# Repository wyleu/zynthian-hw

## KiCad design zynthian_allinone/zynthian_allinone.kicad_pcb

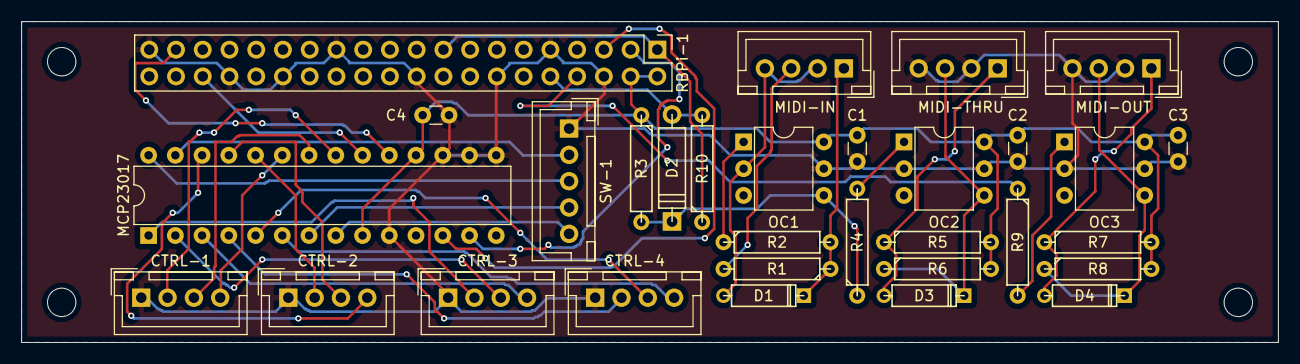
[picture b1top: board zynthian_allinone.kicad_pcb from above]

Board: 2 copper layers, 119.4 x 30.5 mm, 35 parts (0 on the bottom side), 36 nets.

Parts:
C1, C2, C3, C4: 100n; C_Disc_D3.0mm_W1.6mm_P2.50mm
CTRL-1: CTRL1; JST_XH_B04B-XH-A_04x2.50mm_Straight
CTRL-2: CTRL2; JST_XH_B04B-XH-A_04x2.50mm_Straight
CTRL-3: CTRL3; JST_XH_B04B-XH-A_04x2.50mm_Straight
CTRL-4: CTRL4; JST_XH_B04B-XH-A_04x2.50mm_Straight
D1, D3, D4: 1N4148; D3
D2: 1N5819; D4
MCP23017: MCP23017; DIP-28_W7.62mm
MH1, MH2, MH3, MH4: MountingHole_2.7mm_M2.5_DIN965
MIDI-1: MIDI-IN; JST_XH_B04B-XH-A_04x2.50mm_Straight
MIDI-2: MIDI-THRU; JST_XH_B04B-XH-A_04x2.50mm_Straight
MIDI-3: MIDI-OUT; JST_XH_B04B-XH-A_04x2.50mm_Straight
OC1, OC2, OC3: H11L1; DIP-6_W7.62mm
R1: 100; R4
R2, R6, R8: 470; R4
R3, R4, R9: 1K; R4
R5, R7: 4K7; R4
R10: 10K; R4
RBPi-1: RBPi GPIO; Pin_Header_Straight_2x20_Pitch2.54mm
SW-1: SW1; JST_XH_B05B-XH-A_05x2.50mm_Straight

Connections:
+3V3: R10.1, RBPi-1.1, RBPi-1.17
+5V: C1.1, C2.1, C3.1, C4.1, MCP23017.9, MCP23017.18, OC1.6, OC2.6, OC3.6, R3.1, R5.2, R6.2, R7.2, R8.2, RBPi-1.2, RBPi-1.4
/INTA: MCP23017.20, RBPi-1.36
/INTB: MCP23017.19, RBPi-1.37
/MIDI-IN: D2.2, R10.2, RBPi-1.10
/MIDI-OUT: R9.1, RBPi-1.8
/MIDI-THRU: OC2.1, R4.2
GND: C1.2, C2.2, C3.2, C4.2, CTRL-1.1, CTRL-2.1, CTRL-3.1, CTRL-4.1, MCP23017.10, MCP23017.15, MCP23017.16, MCP23017.17, MIDI-2.2, MIDI-2.4, MIDI-3.2, MIDI-3.4, OC1.5, OC2.2, OC2.5, OC3.2, OC3.5, RBPi-1.6, RBPi-1.9, RBPi-1.14, RBPi-1.20, RBPi-1.25, RBPi-1.30, RBPi-1.34, RBPi-1.39, SW-1.1
unnamed: CTRL-1.2, MCP23017.21
unnamed: CTRL-1.3, MCP23017.22
unnamed: CTRL-1.4, MCP23017.23
unnamed: CTRL-2.2, MCP23017.24
unnamed: CTRL-2.3, MCP23017.25
unnamed: CTRL-2.4, MCP23017.26
unnamed: CTRL-3.2, MCP23017.1
unnamed: CTRL-3.3, MCP23017.2
unnamed: CTRL-3.4, MCP23017.3
unnamed: CTRL-4.2, MCP23017.4
unnamed: CTRL-4.3, MCP23017.5
unnamed: CTRL-4.4, MCP23017.6
unnamed: D1.1, MIDI-1.1, R1.1, R2.2
unnamed: D1.2, MIDI-1.2, MIDI-1.4, OC1.2
unnamed: D2.1, OC1.4, R3.2, R4.1
unnamed: D3.1, MIDI-2.3, OC2.4, R6.1
unnamed: D3.2, MIDI-2.1, R5.1
unnamed: D4.1, MIDI-3.3, OC3.4, R8.1
unnamed: D4.2, MIDI-3.1, R7.1
unnamed: MCP23017.7, SW-1.4
unnamed: MCP23017.8, SW-1.5
unnamed: MCP23017.12, RBPi-1.5
unnamed: MCP23017.13, RBPi-1.3
unnamed: MCP23017.27, SW-1.2
unnamed: MCP23017.28, SW-1.3
unnamed: MIDI-1.3, R1.2
unnamed: OC1.1, R2.1
unnamed: OC3.1, R9.2
